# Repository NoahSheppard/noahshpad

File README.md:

# Noah's Macropad

An 8-key custom macropad with a fancy pantsy OLED screen

## Photos of my beautiful hackpad

### Overall Hackpad

### Schematic

### PCB

## BOM

| Part Name | Quantity |
|---|---:|
| Case | 1 |
| Seeed XIAO RP2040 | 1 |
| through-hole 1N4148 Diode | 8 |
| MX-Style Switch | 8 |
| DSA Keycap | 8 |

## Production Files

Current production outputs included in this repo:

- PCB Gerbers and drill files -> `production/gerbers/` and `production/gerbers.zip`
- Full CAD export -> `production/oled-v2.3mf`
- Bodies -> `production/Base.step` and `Top Plate.step` respectively

## Author

Noah Sheppard (noahshdev)

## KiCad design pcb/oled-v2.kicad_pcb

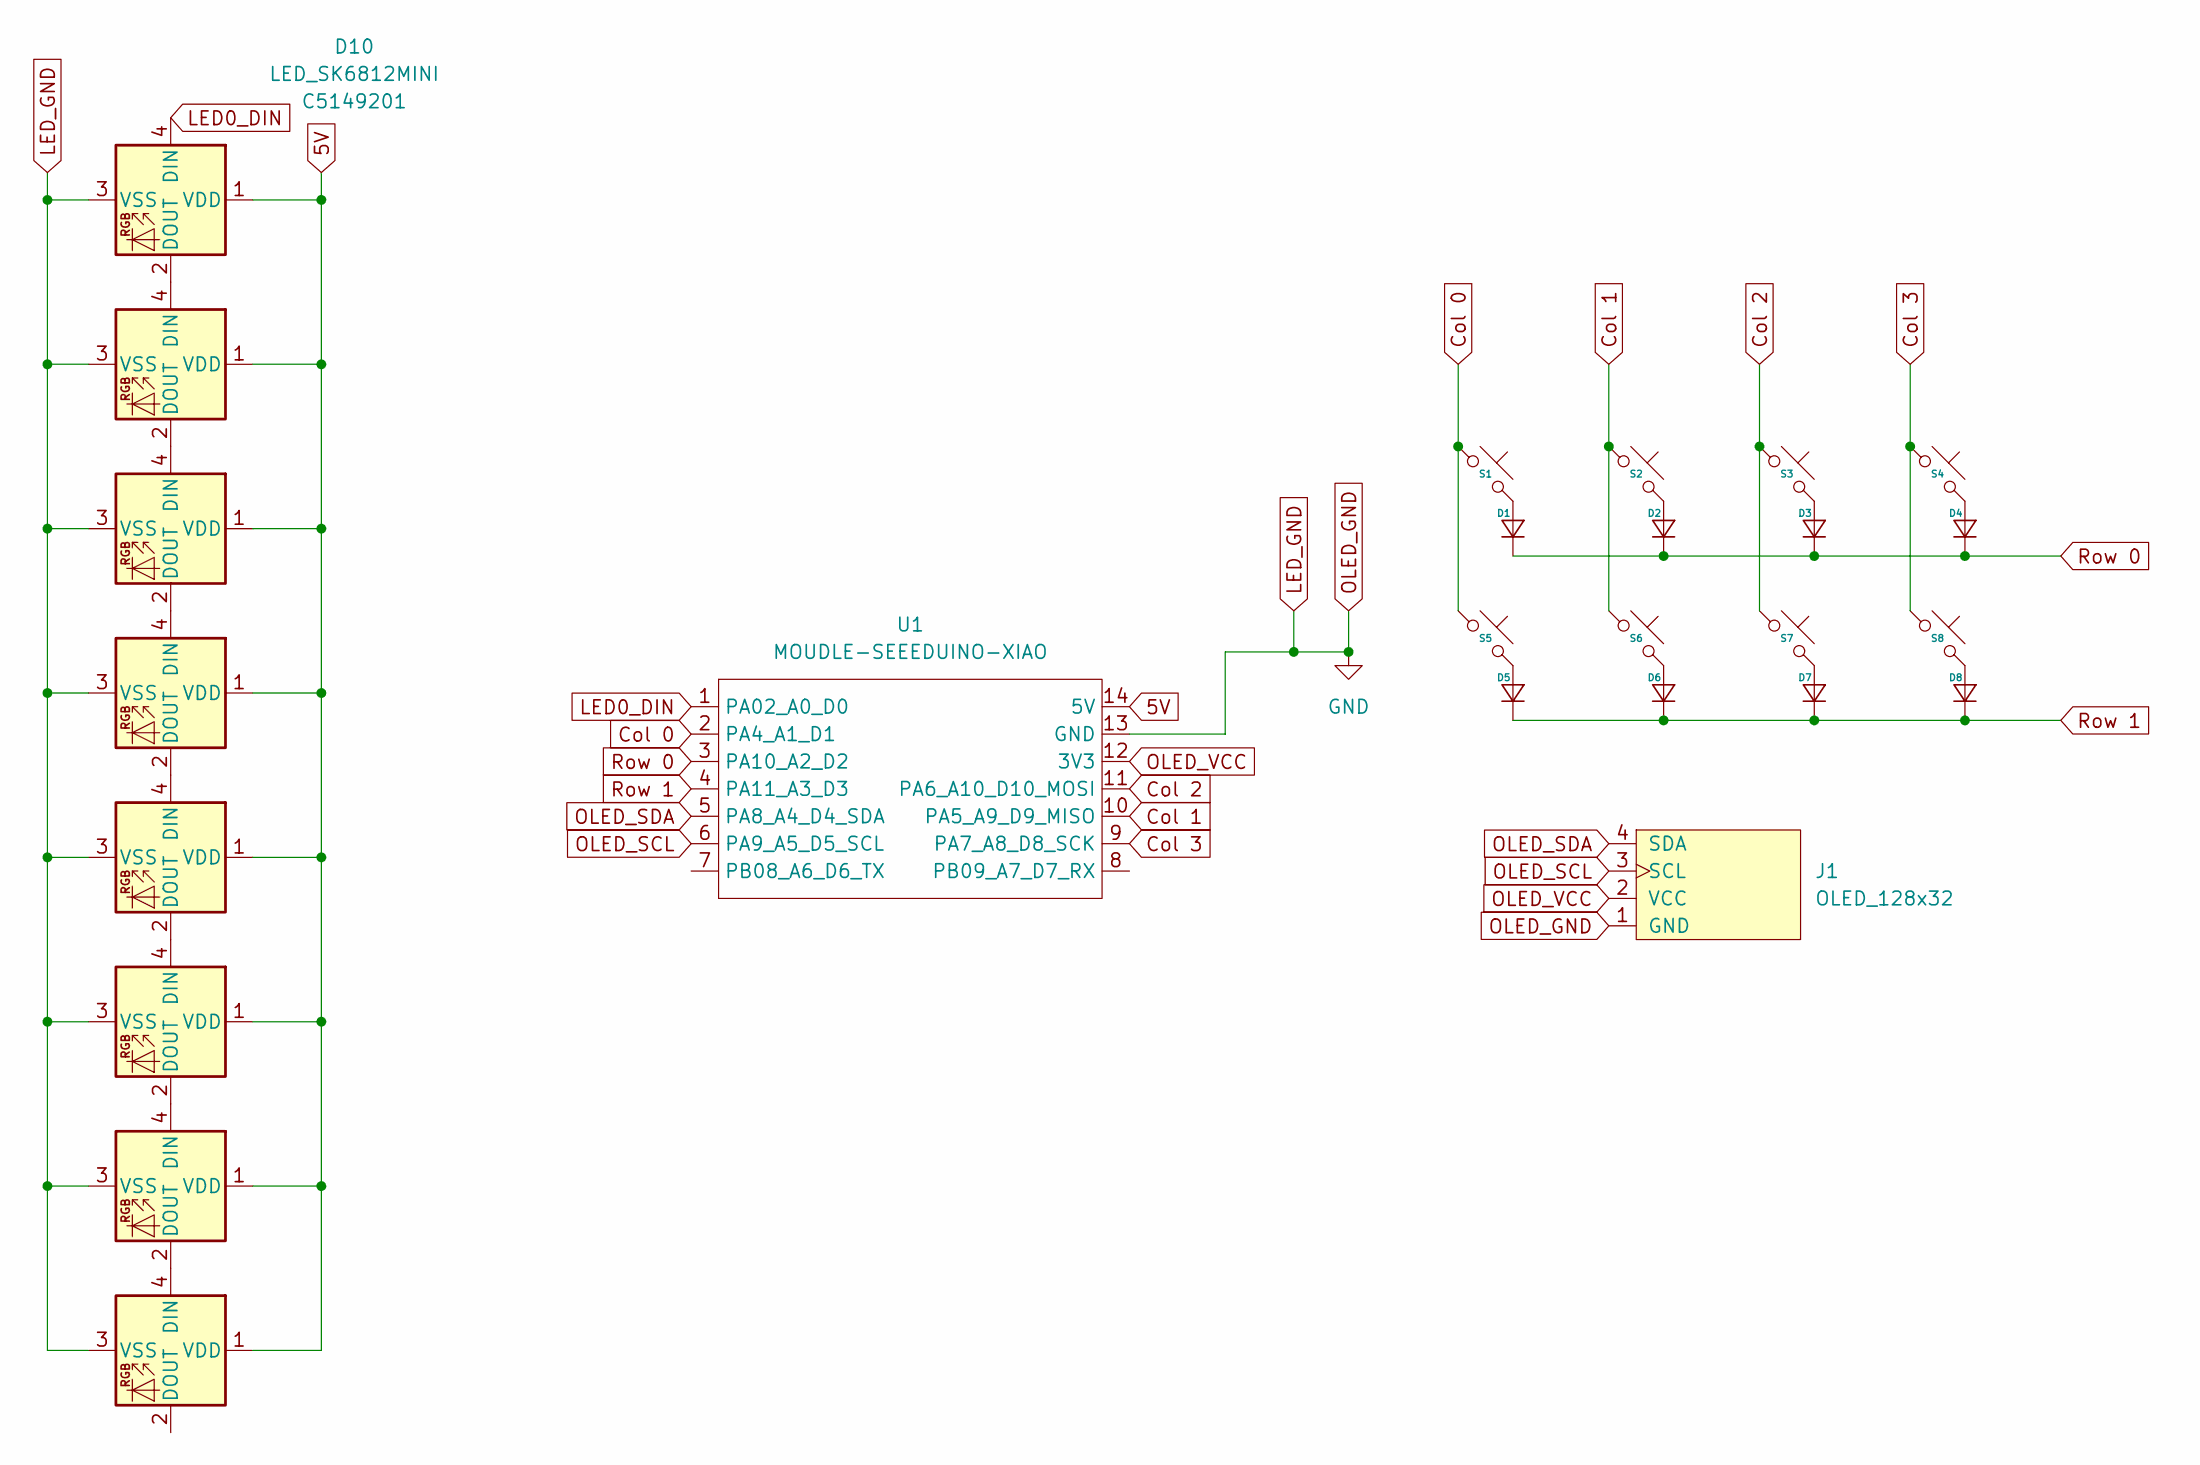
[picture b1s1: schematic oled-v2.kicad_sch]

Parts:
D1, D2, D3, D4, D5, D6, D7, D8: Diode_DO-35
D9, D10, D11, D12, D13, D14, D15, D16: LED_SK6812MINI; LCSC C5149201
J1: OLED_128x32
S1, S2, S3, S4, S5, S6, S7, S8: SW_Cherry_MX_1.00u_PCB
U1: MOUDLE-SEEEDUINO-XIAO; XIAO-Generic-Hybrid-14P-2.54-21X17.8MM

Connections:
5V: D9.1 (VDD), D10.1 (VDD), D11.1 (VDD), D12.1 (VDD), D13.1 (VDD), D14.1 (VDD), D15.1 (VDD), D16.1 (VDD), U1.14 (5V)
Col 0: S1.1, S5.1, U1.2 (PA4_A1_D1)
Col 1: S2.1, S6.1, U1.10 (PA5_A9_D9_MISO)
Col 2: S3.1, S7.1, U1.11 (PA6_A10_D10_MOSI)
Col 3: S4.1, S8.1, U1.9 (PA7_A8_D8_SCK)
LED0_DIN: D10.4 (DIN), U1.1 (PA02_A0_D0)
LED_GND: D9.3 (VSS), D10.3 (VSS), D11.3 (VSS), D12.3 (VSS), D13.3 (VSS), D14.3 (VSS), D15.3 (VSS), D16.3 (VSS), J1.1 (GND), U1.13 (GND)
unnamed: D1.2 (A), S1.2
unnamed: D2.2 (A), S2.2
unnamed: D3.2 (A), S3.2
unnamed: D4.2 (A), S4.2
unnamed: D5.2 (A), S5.2
unnamed: D6.2 (A), S6.2
unnamed: D7.2 (A), S7.2
unnamed: D8.2 (A), S8.2
unnamed: D9.4 (DIN), D10.2 (DOUT)
unnamed: D9.2 (DOUT), D11.4 (DIN)
unnamed: D11.2 (DOUT), D12.4 (DIN)
unnamed: D12.2 (DOUT), D13.4 (DIN)
unnamed: D13.2 (DOUT), D14.4 (DIN)
unnamed: D14.2 (DOUT), D15.4 (DIN)
unnamed: D15.2 (DOUT), D16.4 (DIN)
OLED_SCL: J1.3 (SCL), U1.6 (PA9_A5_D5_SCL)
OLED_SDA: J1.4 (SDA), U1.5 (PA8_A4_D4_SDA)
OLED_VCC: J1.2 (VCC), U1.12 (3V3)
Row 0: D1.1 (K), D2.1 (K), D3.1 (K), D4.1 (K), U1.3 (PA10_A2_D2)
Row 1: D5.1 (K), D6.1 (K), D7.1 (K), D8.1 (K), U1.4 (PA11_A3_D3)

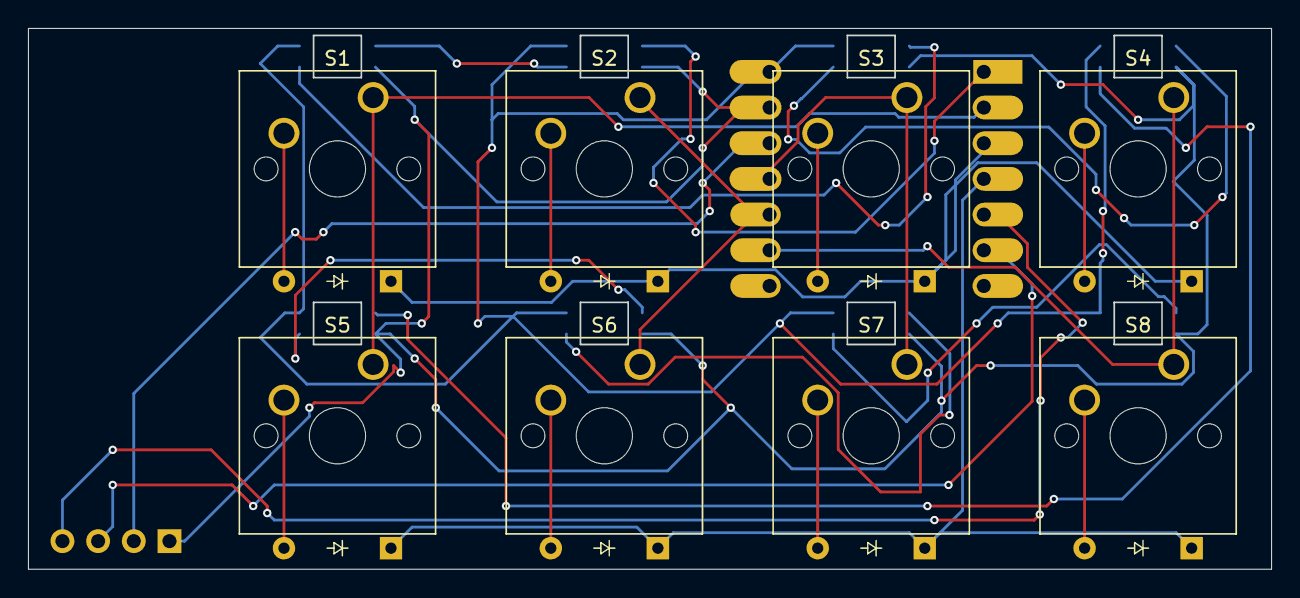
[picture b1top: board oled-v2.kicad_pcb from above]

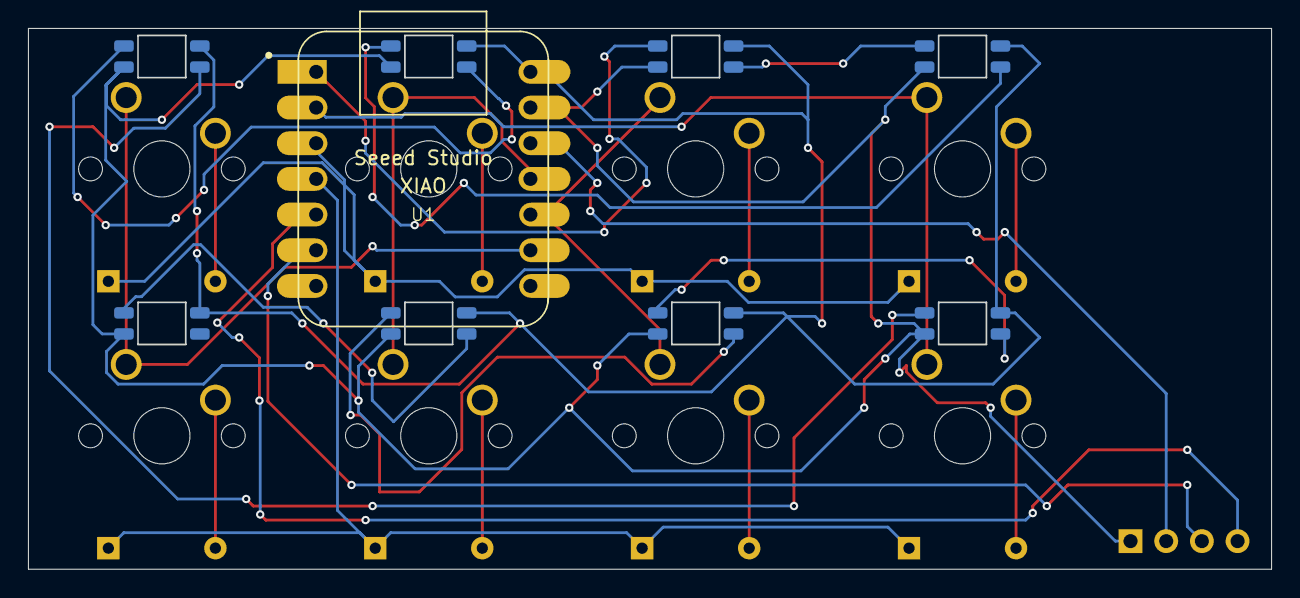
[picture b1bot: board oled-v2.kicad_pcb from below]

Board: 2 copper layers, 88.4 x 38.4 mm, 26 parts (9 on the bottom side), 27 nets.

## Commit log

2026-02-18 init commit
2026-02-18 bom and readme
2026-02-19 moved things around, to make it look less like an offcentered brick
2026-02-19 finished PCB - my dumbass had the SEEED Xiao mounted to the front of the PCB in which it would be "below" a switch (wouldn't be phsycially possible) - put it on the bottom you say? With the way I did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
2026-02-20 de ai'ified the readme and updated it with little info
2026-02-20 forgot to checkout in vsc so hopefully this merge works - meaninigless change for this commit lmao
2026-02-20 Initial layering firmware, with great help from my trusty ol friend AI. I plan to have the keys in each layer changable through a GUI maybe? That could be pretty cool + hours for flavortown
2026-02-20 reset firmware in git because it broke git somehow :(
2026-02-20 new firmware woohoo
2026-02-21 added doom
2026-02-21 doom* (*in theory)
2026-02-26 turns out I had my GND wired to 5V - fixed now.
    production/oled-v2.3mf = full CAD file
    images updated
2026-02-26 update readme to account for stupidity
2026-03-11 rewired lights, needs checking through
2026-03-23 3d printer case files cause i left the old case in the sun and need to redo the files for a different printer lol
